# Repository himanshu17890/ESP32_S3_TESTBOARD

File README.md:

# ESP32-S3 IoT Development Board (KiCad PCB Design)

A custom **4-layer ESP32-S3 IoT development board** designed in **KiCad** for embedded and IoT applications.

> **Project Status:** PCB Design Completed (Not Fabricated)

---

# Project Overview

This project focuses on the complete schematic capture and PCB layout of an ESP32-S3 based development board intended for IoT and embedded system applications.

The board was designed following good PCB design practices, including component placement, routing, power distribution, USB differential pair routing, and design rule verification.

This repository contains the complete KiCad design files for learning, portfolio, and reference purposes.

---

# Features

- ESP32-S3-WROOM module
- 4-Layer PCB Design
- USB Type-C Interface
- USB ESD Protection
- 3.3V Power Regulation
- BOOT and RESET Buttons
- UART Programming Header
- QWIIC (I²C) Connector
- GPIO Expansion Header
- Power Status LED
- Design Rule Check (DRC) Verified
- Electrical Rule Check (ERC) Verified

---

# Tools Used

- KiCad 9
- PCB Editor
- Schematic Editor
- Interactive Router
- 3D Viewer

---

# Design Highlights

- Designed complete schematic from scratch
- Created 4-layer PCB layout
- Routed USB differential pair
- Implemented proper power distribution
- Added decoupling capacitors following ESP32 recommendations
- Implemented USB ESD protection
- Added programming and debugging interfaces
- Planned antenna keep-out region
- Performed ERC and DRC verification

---

# Hardware Specifications

| Feature | Details |
|----------|---------|
| MCU | ESP32-S3-WROOM |
| PCB Layers | 4 |
| USB | USB Type-C |
| Power | 3.3V |
| Programming | UART |
| Communication | UART, SPI, I²C |
| Expansion | QWIIC Connector |
| Design Software | KiCad 9 |

---

# Repository Structure

```
ESP32_S3_TESTBOARD
│
├── Hardware
│   ├── ESP32_S3_TESTBOARD.kicad_pro
│   ├── ESP32_S3_TESTBOARD.kicad_sch
│   └── ESP32_S3_TESTBOARD.kicad_pcb
│
├── Images
│   ├── PCB_Top.png
│   ├── PCB_Bottom.png
│   ├── 3D_Top.png
│   ├── 3D_Bottom.png
│   └── Schematic.png
│
├── Documents
│
├── README.md
├── LICENSE
└── .gitignore
```

---

# Images

## Schematic 

---

## PCB Top

## 3D Top View

---

## 3D Bottom View

---

# PCB Design Workflow

1. Component Selection
2. Schematic Capture
3. Footprint Assignment
4. PCB Floor Planning
5. Component Placement
6. Interactive Routing
7. USB Differential Pair Routing
8. Power Plane Design
9. ERC Verification
10. DRC Verification
11. 3D Inspection

---

# Learning Outcomes

Through this project I gained practical experience in:

- Multi-layer PCB Design
- Schematic Capture
- ESP32 Hardware Design
- USB Interface Design
- PCB Component Placement
- Differential Pair Routing
- Power Distribution
- PCB Design Rules
- ERC and DRC Validation
- KiCad PCB Design Workflow

---

# Future Improvements

- PCB Fabrication
- Board Assembly
- Hardware Bring-up
- Firmware Development
- Functional Testing
- Power Consumption Analysis
- Sensor Expansion

---

# Note

This repository contains the **PCB design only**.

The hardware has **not been fabricated or tested**, and this project is intended to demonstrate PCB design skills using KiCad.

---

# Author

**Himanshu Pawar**

Electronics & Telecommunication Engineer

- LinkedIn: https://www.linkedin.com/in/himanshu-pawar-a74b732a9
- GitHub: https://github.com/himanshu17890

---

If you found this project useful, consider giving it a ⭐.

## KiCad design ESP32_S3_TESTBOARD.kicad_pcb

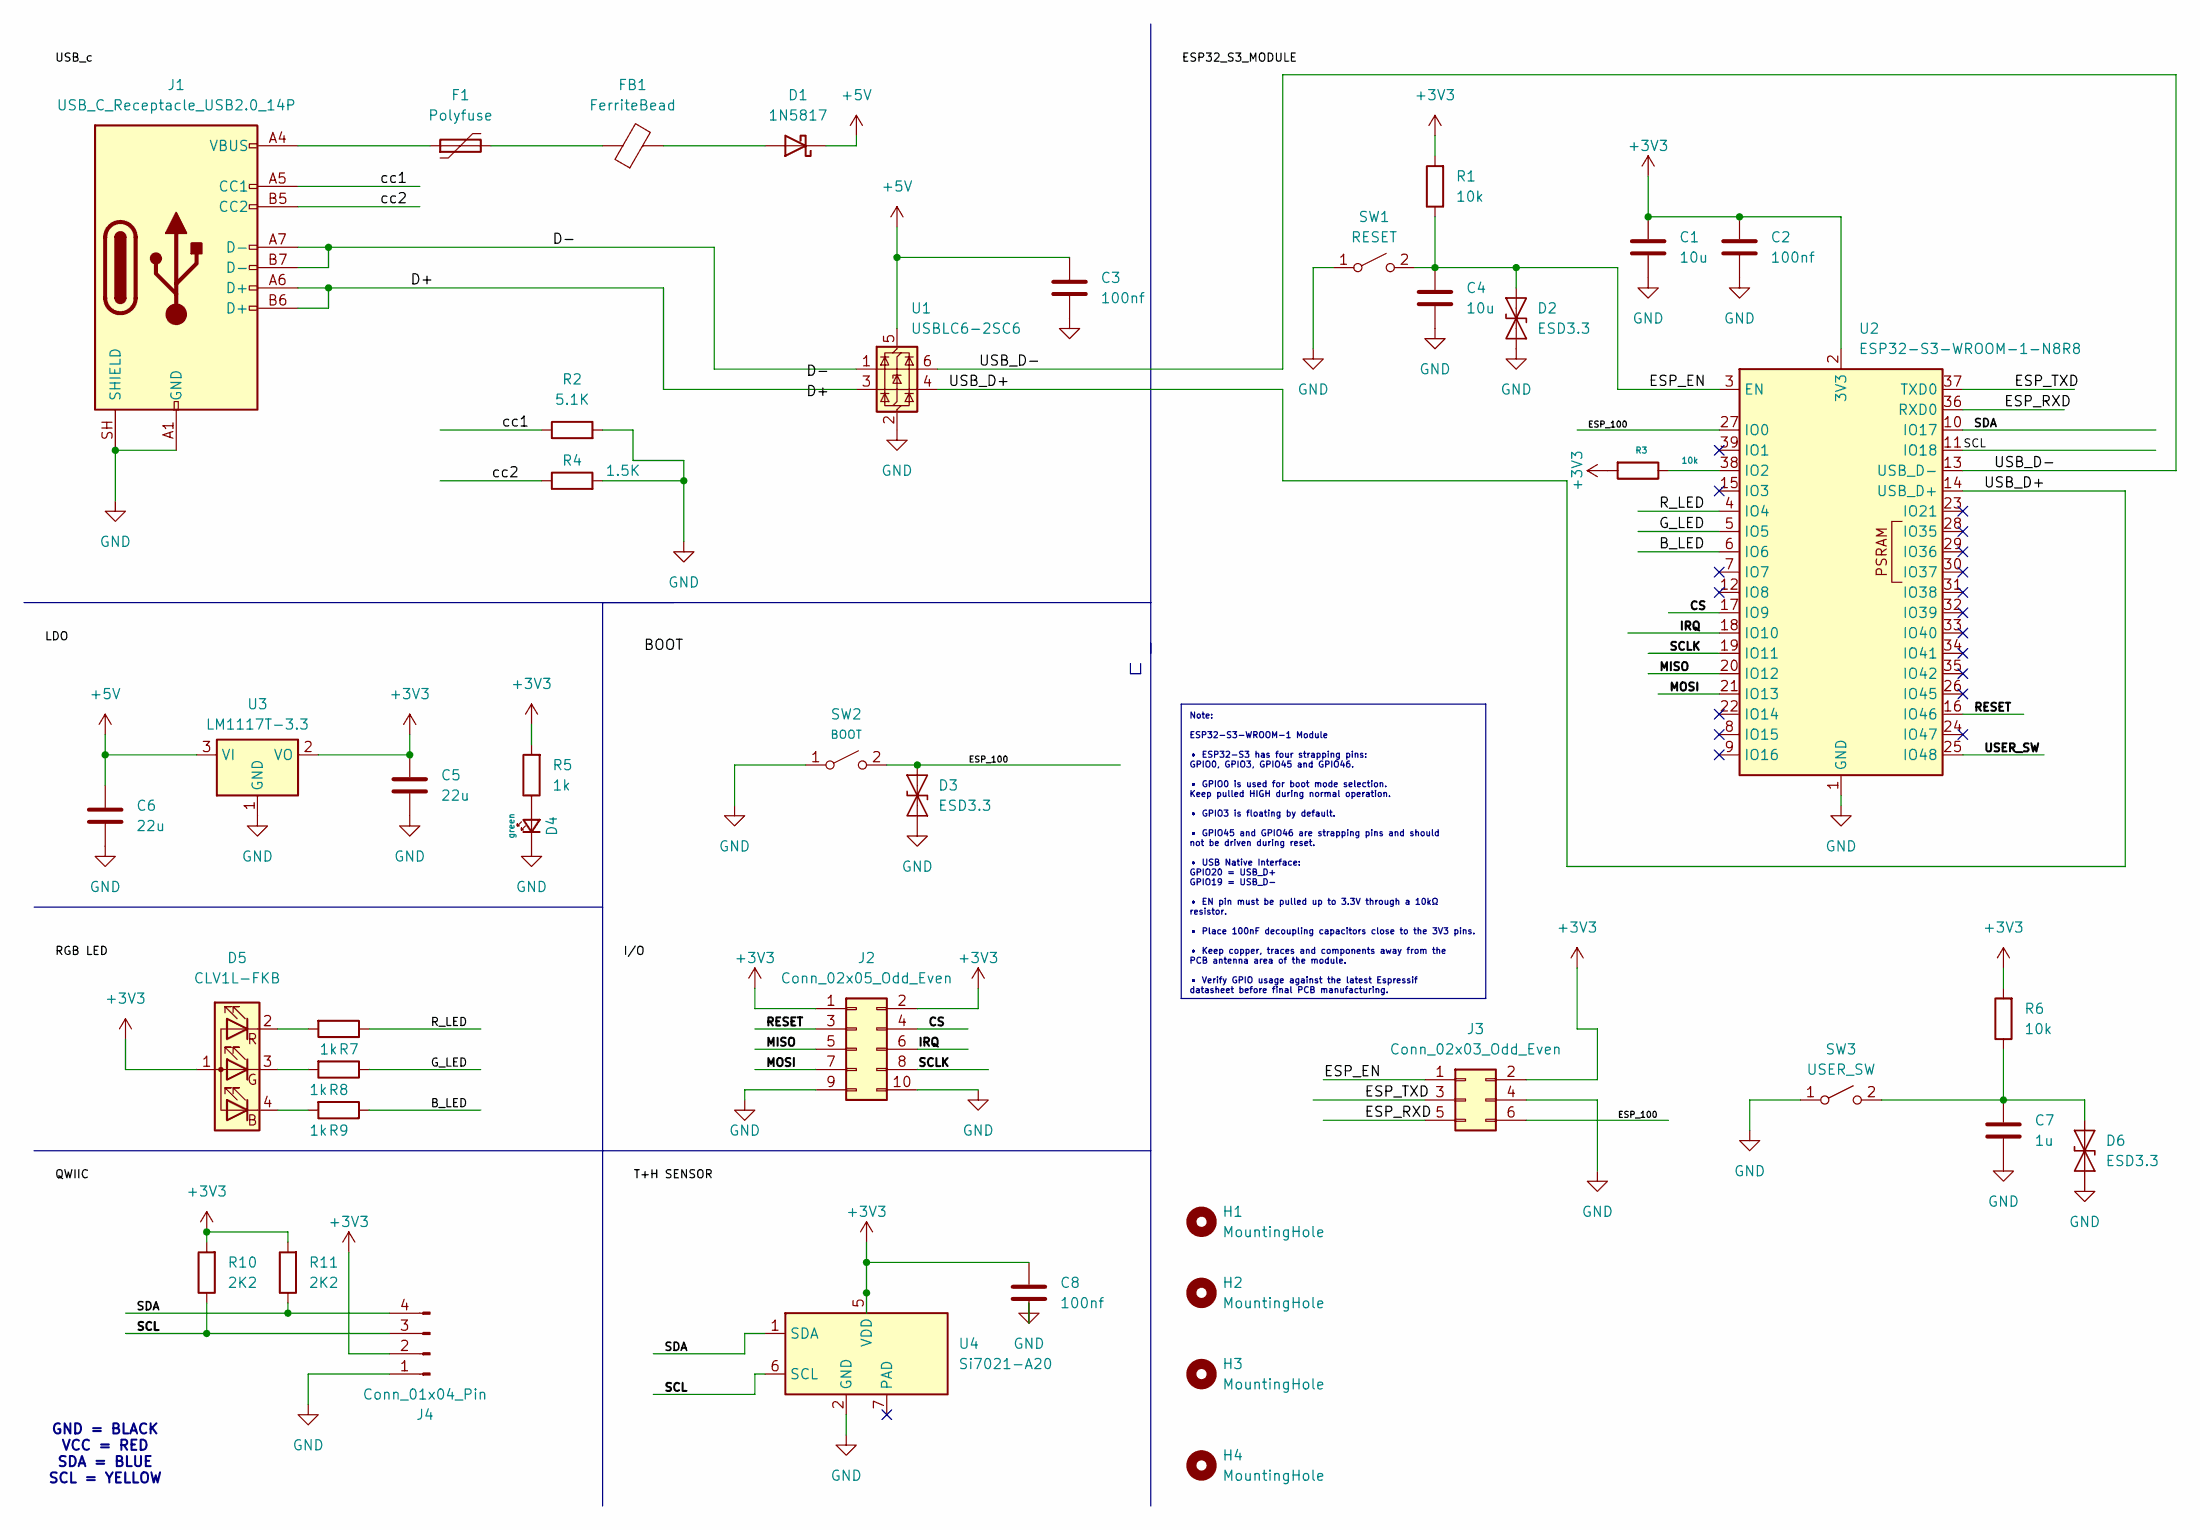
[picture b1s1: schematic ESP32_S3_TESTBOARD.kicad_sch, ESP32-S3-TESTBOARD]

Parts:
C1, C4: 10u; C_0603_1608Metric
C2, C8: 100nf; C_0402_1005Metric_Pad0.74x0.62mm_HandSolder
C3: 100nf
C5, C6: 22u; C_0603_1608Metric
C7: 1u; C_0603_1608Metric
D1: 1N5817; D_SMA
D2, D3, D6: ESD3.3; D_SOD-923
D4: green; LED_0603_1608Metric
D5: CLV1L-FKB; LED_Cree-PLCC4_3.2x2.8mm_CCW
F1: Polyfuse; Fuse_1206_3216Metric
FB1: FerriteBead; L_0603_1608Metric
H1, H2, H3, H4: MountingHole; MountingHole_3.2mm_M3
J1: USB_C_Receptacle_USB2.0_14P; USB_C_Receptacle_GCT_USB4105-xx-A_16P_TopMnt_Horizontal
J2: Conn_02x05_Odd_Even; PinHeader_2x05_P2.54mm_Vertical
J3: Conn_02x03_Odd_Even; PinHeader_2x03_P2.54mm_Vertical
J4: Conn_01x04_Pin; JST_SH_SM04B-SRSS-TB_1x04-1MP_P1.00mm_Horizontal
R1, R3, R6: 10k; R_0603_1608Metric
R2: 5.1K; R_0603_1608Metric
R4: 1.5K; R_0603_1608Metric
R5, R7, R8, R9: 1k; R_0603_1608Metric
R10, R11: 2K2; R_0603_1608Metric
SW1: RESET; SW_SPST_SKQG_WithoutStem
SW2: BOOT; SW_SPST_SKQG_WithoutStem
SW3: USER_SW; SW_SPST_TL3342
U1: USBLC6-2SC6; SOT-23-6
U2: ESP32-S3-WROOM-1-N8R8; ESP32-S3-WROOM-1
U3: LM1117T-3.3; SOT-223-3_TabPin2
U4: Si7021-A20; DFN-6-1EP_3x3mm_P1mm_EP1.5x2.4mm

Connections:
+3V3: C1.1, C2.1, C5.1, C8.1, D5.1 (A), J2.1, J2.2, J3.2, J4.2, R1.2, R3.2, R5.2, R6.2, R10.2, R11.2, U2.2 (3V3), U3.2 (VO), U4.5 (VDD)
+5V: C3.1, C6.1, D1.1 (K), U1.5 (VBUS), U3.3 (VI)
/B_LED: R9.1, U2.6 (IO6)
/CS: J2.4, U2.17 (IO9)
/D+: J1.A6 (D+), J1.B6 (D+), U1.3 (I/O2)
/D-: J1.A7 (D-), J1.B7 (D-), U1.1 (I/O1)
/ESP_100: D3.2 (A2), J3.6, SW2.2 (B), U2.27 (IO0)
/ESP_EN: C4.1, D2.2 (A2), J3.1, R1.1, SW1.2 (B), U2.3 (EN)
/ESP_RXD: J3.5, U2.36 (RXD0)
/ESP_TXD: J3.3, U2.37 (TXD0)
/G_LED: R8.1, U2.5 (IO5)
/IRQ: J2.6, U2.18 (IO10)
/MISO: J2.5, U2.20 (IO12)
/MOSI: J2.7, U2.21 (IO13)
/RESET: J2.3, U2.16 (IO46)
/R_LED: R7.1, U2.4 (IO4)
/SCL: J4.3, R10.1, U2.11 (IO18), U4.6 (SCL)
/SCLK: J2.8, U2.19 (IO11)
/SDA: J4.4, R11.1, U2.10 (IO17), U4.1 (SDA)
/USB_D+: U1.4 (I/O2), U2.14 (USB_D+)
/USB_D-: U1.6 (I/O1), U2.13 (USB_D-)
/USER_SW: U2.25 (IO48)
/cc1: J1.A5 (CC1), R2.1
/cc2: J1.B5 (CC2), R4.1
GND: C1.2, C2.2, C3.2, C4.2, C5.2, C6.2, C7.2, C8.2, D2.1 (A1), D3.1 (A1), D4.1 (K), D6.1 (A1), J1.A1 (GND), J1.A12 (GND), J1.B1 (GND), J1.B12 (GND), J1.SH (SHIELD), J2.9, J2.10, J3.4, J4.1, R2.2, R4.2, SW1.1 (A), SW2.1 (A), SW3.1 (A), U1.2 (GND), U2.1 (GND), U2.40 (GND), U2.41 (GND), U3.1 (GND), U4.2 (GND)
unnamed: D1.2 (A), FB1.2
unnamed: D4.2 (A), R5.1
unnamed: D5.4 (BK), R9.2
unnamed: D5.3 (GK), R8.2
unnamed: D5.2 (RK), R7.2
unnamed: C7.1, D6.2 (A2), R6.1, SW3.2 (B)
unnamed: F1.1, J1.A4 (VBUS), J1.A9 (VBUS), J1.B4 (VBUS), J1.B9 (VBUS)
unnamed: F1.2, FB1.1
unnamed: R3.1, U2.38 (IO2)

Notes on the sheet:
GND = BLACK VCC = RED SDA = BLUE SCL = YELLOW
Note: ESP32-S3-WROOM-1 Module • ESP32-S3 has four strapping pins: GPIO0, GPIO3, GPIO45 and GPIO46. • GPIO0 is used for boot mode selection. Keep pulled HIGH during normal operation. • GPIO3 is floating by default. • GPIO45 and GPIO46 are strapping pins and should not be driven during reset. • USB N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

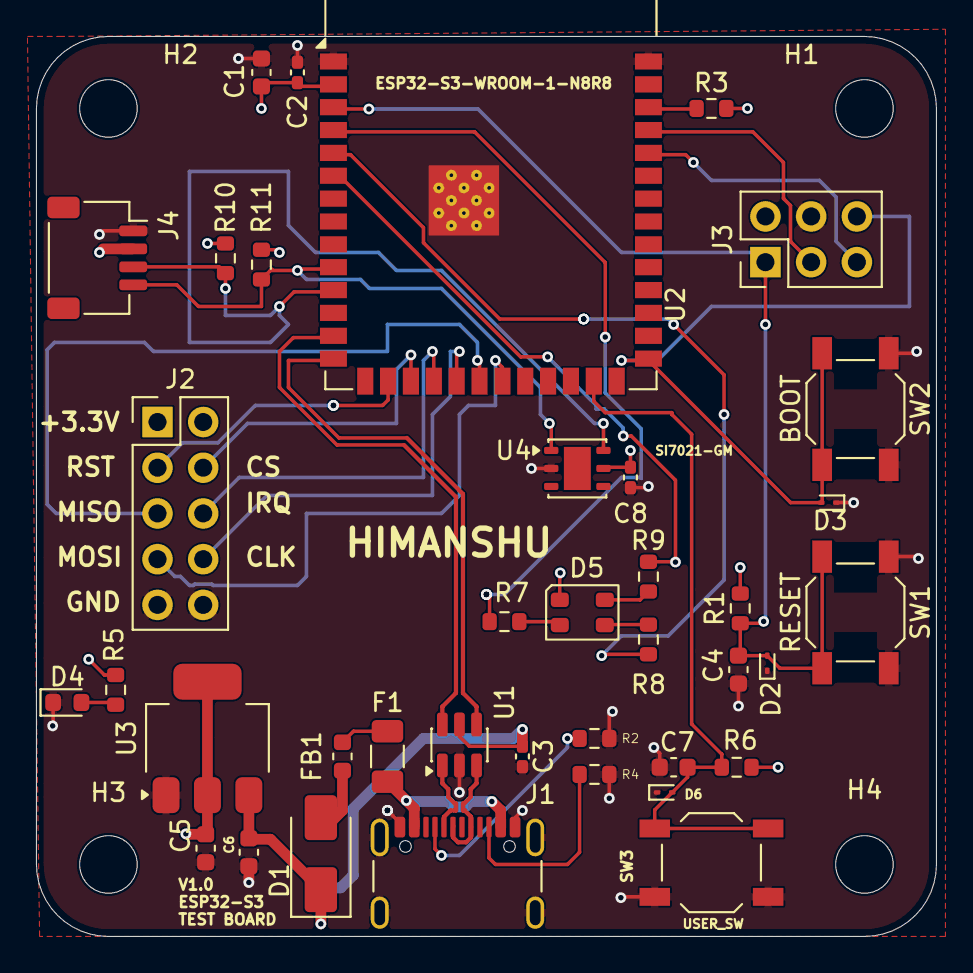
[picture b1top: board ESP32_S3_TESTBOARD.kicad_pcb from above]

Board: 4 copper layers, 50.0 x 50.0 mm, 42 parts (0 on the bottom side), 33 nets.
